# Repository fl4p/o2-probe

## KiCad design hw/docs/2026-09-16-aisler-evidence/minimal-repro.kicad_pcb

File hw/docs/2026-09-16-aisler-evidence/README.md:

# Attachments for the AISLER ODB++ bug report

Evidence for [`../2026-09-16-aisler-push-odb-bug-report.md`](../2026-09-16-aisler-push-odb-bug-report.md).
These files live in the repository rather than a scratch directory because the
email offers them to AISLER support and they have to still exist when it is sent.

Every archive is what AISLER Push for KiCad 0.3.2 uploads, reproduced by
`.work/aisler/plugin_export.py`, which mirrors `push_thread.py`'s `run()`. The
`-withodb` / `-noodb` pairs differ by exactly one file, `odb.zip`.

| file | board | `odb.zip` | AISLER result |
|---|---|---|---|
| `ring-board-withodb.zip` | o2-probe Rev B ring, 20 × 86 mm, as designed | present | **Failed to prepare production data** |
| `ring-board-noodb.zip` | the same board | absent | ready — 20 × 86 mm, 2 layers, 0.2 mm drill, 4 elongated holes |
| `minimal-repro-withodb.zip` | the same board with all 2 414 tracks, 209 vias and 6 zones deleted; 87 footprints remain | present | **Failed to prepare production data** |
| `minimal-repro-noodb.zip` | the same stripped board | absent | ready |
| `minimal-repro.kicad_pcb` | the stripped board's source, for regenerating the pair | — | — |

The stripped pair is the useful one: its ODB++ holds 171 + 98 copper features,
fewer than any board that passes, so the failure is not a size or complexity
limit and is not in the routing.

Regenerate the pair:

```sh
curl -sSL -o plugin.zip https://packages.aisler.net/packages/2/download.zip   # sha256 bec5d737…eaac7
unzip -q plugin.zip -d plugin
echo '[["minimal-repro.kicad_pcb", "minimal-repro"]]' > job.json
AISLER_PLUGIN=$PWD/plugin /Applications/KiCad/KiCad.app/Contents/Frameworks/\
Python.framework/Versions/Current/bin/python3 plugin_export.py job.json
```

The export is deterministic: regenerating `minimal-repro-withodb.zip` a day
later reproduced the same 120 636 bytes.

SHA-256, recorded 2026-09-17:

```
c4b9463b58eb1498b564fe7bf5fb34deeadce6d148de53e59035b362dfdfa857  ring-board-withodb.zip
8586fd3505299d39fc1c73bb0f78423b0f15299fd99de2e95ad06cf56704d3c8  ring-board-noodb.zip
2412fb023a44e78f6d54c754103e811d4520491e386fb5d053730aa02366c47c  minimal-repro-withodb.zip
a60e0cec4c7bf21ca470760ce594d1d681b986d30b5ac14b49875b40cfcda060  minimal-repro-noodb.zip
2b5e7ed2d0c3d2e374e1431b3a10d20b26c5f440e95150c99e8ad3eb1c4e7c74  minimal-repro.kicad_pcb
```

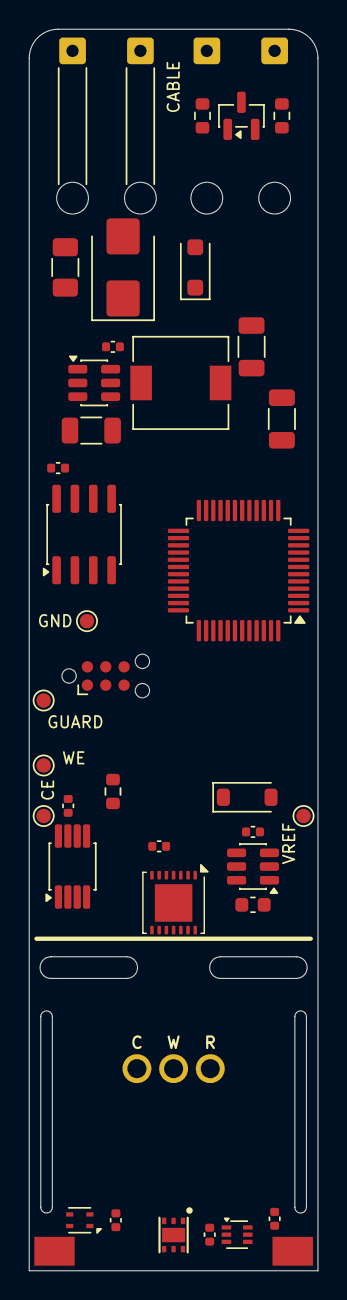
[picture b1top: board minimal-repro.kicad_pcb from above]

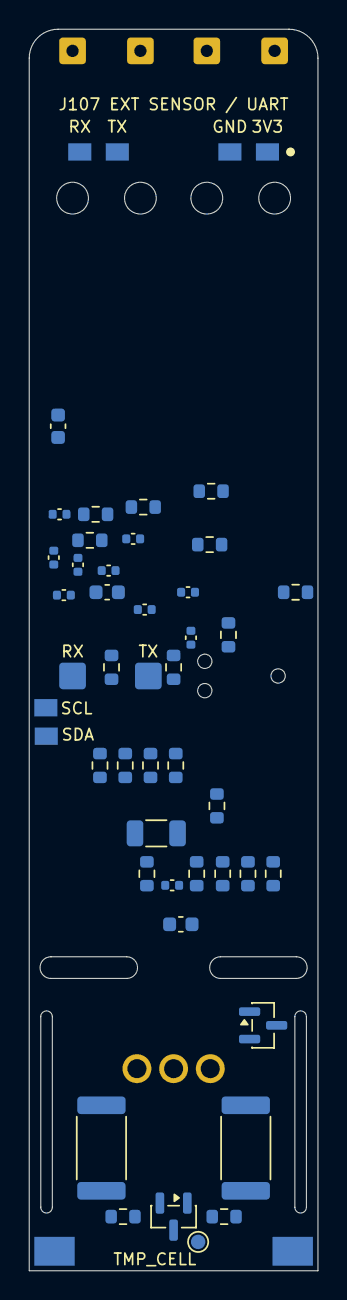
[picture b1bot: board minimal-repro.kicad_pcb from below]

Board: 2 copper layers, 20.0 x 86.0 mm, 87 parts (46 on the bottom side), 46 nets, no tracks yet.

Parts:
C1, C7: 10u 25V X7R; C_1206_3216Metric
C2, C11, C12, C13, C15, C16, C20, C21, C25, C26, C28, C30, C31, C32, C33, C34, C35, C36: 100n; C_0402_1005Metric
C3, C4: 22u; C_1206_3216Metric
C8: 1u; C_0603_1608Metric
C10, C14: 4.7u; C_0603_1608Metric
C17: 10n; C_0603_1608Metric
D1: SMBJ15A-13-F; D_SMB
D2: SM712-02HTG; SOT-23
D3: PMEG4010CEH; D_SOD-123F
D7: TPD2E2U06-Q1; SOT-23
D8: BAT54W-G; D_SOD-123
F1: 0.75A PTC; PTC_1206_3216Metric
J3: TC2030 SWD PRE-POT; Tag-Connect_TC2030-IDC-NL_2x03_P1.27mm_Vertical
J5: HEATED MEMBRANE RING; Heater_Ring_Lands
J101: J1.1 BROWN +12V; SolderWire-0.25sqmm_1x01_D0.65mm_OD1.7mm_Relief
J102: J1.2 WHITE GND; SolderWire-0.25sqmm_1x01_D0.65mm_OD1.7mm_Relief
J103: J1.3 GREEN A; SolderWire_RaisedRelief_1x01
J104: J1.4 YELLOW B; SolderWire_RaisedRelief_1x01
J105: BRIDGE TX (PA2); SolderPad_SMD_J105
J106: BRIDGE RX (PA3); SolderPad_SMD_J106
J107: EXT SENSOR / UART PADS; SolderPads_1x04_SMD_PwrUart
J108: EXT SENSOR SDA; SolderPad_SMD_I2C_SDA
J109: EXT SENSOR SCL; SolderPad_SMD_I2C_SCL
L1: 4.7u SHIELDED; L_6.3x6.3_H3
Q2: AO3400A; SOT-23
R2, R3, R32: 10R; R_0603_1608Metric
R4: 120R DNP; R_0603_1608Metric
R7, R24, R45: 47k; R_0603_1608Metric
R9, R17, R29: 100k; R_0603_1608Metric
R10, R11: 4.7k; R_0603_1608Metric
R25: 27k; R_0603_1608Metric
R26, R43, R44: 91k 1%; R_0603_1608Metric
R27, R28: 10k; R_0603_1608Metric
R33, R37, R38: 1k; R_0603_1608Metric
R39: DNP 100k; R_0603_1608Metric
R40: 47R; R_0603_1608Metric
R42: 1k 1%; R_0603_1608Metric
RH1, RH2: 280R 1W; R_2512_6332Metric
TP1: CELL_WE; TestPoint_Pad_D1.0mm
TP2: GND; TestPoint_Pad_D1.0mm
TP3: CELL_CE; TestPoint_Pad_D1.0mm
TP4: VREF; TestPoint_Pad_D1.0mm
TP5: GUARD; TestPoint_Pad_D1.0mm
TP6: TMP_CELL_EP; TestPoint_Pad_D1.0mm
U1: AP63203WU-7; TSOT-23-6
U4: OPA2333AIDGKR; VSSOP-8_3x3mm_P0.65mm
U5: THVD1410DR; SOIC-8_3.9x4.9mm_P1.27mm
U6: STM32G071CBT7; LQFP-48_7x7mm_P0.5mm
U7: LMP91000SD/NOPB; WSON-14-1EP_4.0x4.0mm_P0.5mm_EP2.6x2.6mm
U10: TMP117 CELL; TMP117_WSON-6-1EP_2x2mm_TI
U11: SGX-OX-ROHS-Mini; SGX-OX-ROHS-Mini_ISS2
U12: SHT45-AD1F; Sensirion_DFN-4_1.5x1.5mm_P0.8mm_SHT4x_NoCentralPad
U15: REF3425IDBVR; SOT-23-6
U16: TMP302BDRLR; TMP302_DRL6_TI

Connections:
/3V3A: C7.1, C8.1, C16.1, C25.1, R24.1, R32.2, U4.8, U7.6
/3V3D: C3.1, C4.1, C11.1, C12.1, C13.1, C14.1, C20.1, C21.1, C35.1, C36.1, J3.1, J107.1, L1.2, R10.2, R11.2, R32.1, U1.1, U5.8, U6.4, U6.6, U10.4, U10.5, U12.3, U15.3, U15.4, U16.1, U16.4, U16.5, U16.6
/+12V_FUSED: D1.1, D3.2, F1.2
/+12V_RAW: F1.1, J101.1
/+12V_SW: C1.1, D3.1, R26.1, RH1.1, RH2.1, U1.2, U1.3
/ADC_AFE_VOUT: C28.1, R33.2, R39.1, U6.20
/ADC_RE_BUF: C31.1, R38.2, U6.12
/ADC_WE_BUF: C30.1, R37.2, U6.11
/AFE_MENB: R17.1, U6.19, U7.2
/AFE_VOUT: R33.1, U7.8
/BUCK_BST: C2.1, U1.6
/BUCK_SW: C2.2, L1.1, U1.5
/CELL_CE: D7.1, R42.2, TP3.1, U11.1
/CELL_CE_DRV: R42.1, R43.1, U7.14
/CELL_RE: U4.5, U7.13, U11.2
/CELL_WE: TP1.1, U4.3, U7.12, U11.3
/CE_MON: C34.1, R43.2, R44.1, U6.15
/GUARD_REPLICA: R40.2, TP5.1
/HEATER_GATE: Q2.1, R28.2, R29.1, U10.3, U16.3
/HEATER_LOW: J5.1, Q2.3, RH1.2, RH2.2
/HEATER_PWM: R28.1, U6.28
/I2C_SCL: J109.1, R10.1, U6.45, U7.3, U10.1, U12.2
/I2C_SDA: J108.1, R11.1, U6.46, U7.4, U10.6, U12.1
/LMP_C1: C17.1, U7.10
/LMP_C2: C17.2, U7.9
/NRST: C15.1, J3.3, U6.10
/RE_BUF: R38.1, R40.1, U4.6, U4.7
/RS485_A: R2.1, R4.1, U5.6
/RS485_A_CABLE: D2.1, J103.1, R2.2
/RS485_B: R3.1, R4.2, U5.7
/RS485_B_CABLE: D2.2, J104.1, R3.2
/RS485_DE: R7.1, U5.3, U6.30
/RS485_RE: R45.1, U5.2, U6.31
/RS485_RX: U5.1, U6.32
/RS485_TX: U5.4, U6.29
/SWCLK_BOOT0: J3.4, R9.1, U6.36
/SWDIO: J3.2, U6.35
/SWO: J3.6, U6.42
/TMP_CELL_EP: TP6.1, U10.7
/UART2_RX: J106.1, J107.6, U6.14
/UART2_TX: J105.1, J107.5, U6.13
/VA_MON: C33.1, R24.2, R25.1, U6.18
/VIN_MON: C32.1, D8.1, R26.2, R27.1, U6.17
/VREF_TRIM: C10.1, C26.1, TP4.1, U6.5, U7.11, U15.5, U15.6
/WE_BUF: R37.1, U4.1, U4.2
GND: C1.2, C3.2, C4.2, C7.2, C8.2, C10.2, C11.2, C12.2, C13.2, C14.2, C15.2, C16.2, C20.2, C21.2, C25.2, C26.2, C28.2, C30.2, C31.2, C32.2, C33.2, C34.2, C35.2, C36.2, D1.2, D2.3, D7.3, D8.2, J3.5, J102.1, J107.2, Q2.2, R7.2, R9.2, R17.2, R25.2, R27.2, R29.2, R39.2, R44.2, R45.2, TP2.1, U1.4, U4.4, U5.5, U6.7, U7.1, U7.7, U7.15, U10.2, U12.4, U15.1, U15.2, U16.2
